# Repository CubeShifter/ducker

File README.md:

# ducker

A nifty pcb that works as a devboard and can do audio, can be battery powered, and also has a lil breakout board for a keyboard switch and a led.

## Description

I have this fidget that whenever you click it, it makes a loud quacking noise, lights up, and is really cool/annoying. I wanted to try to make my own, and this is my second attempt at doing that. When I started making this project, I came into it with these goals
- make it click
- make it make noise
- pretty low power
- can store audio files
- led
- pretty tiny working space
and I managed to do all of those. It uses a CH552(g i think) chip, has 16mb of flash, usb breakout, can contain a lipo and charge it, has a pam 8302 audio amp, can power an led and has a circuit to cut power supply to it. 
## Getting Started
First of all, you need to get it fabbed. I would reccomend ordering from JLCPCB, and you should probably panelize the pcbs because free pcb.  For actual parts I would reference the BOM, they are 805s and stuff so you can probably hand solder it but PCBA is also fine. All production files are in the repo already :3

As of now, there is no official firmware you should flash it with, but there will probably be some soon. This is also a devboard, so you can play around and do whatever you want with it.

## Authors

just me lol, if you want to talk you can email me at kian@shipwrights.dev i guess :3

## Version History

* 0.6
    * pcbs out, 1.0 will probably be firmware + cad

## License

i think it is mit license so do whatever the hell you want with it i dont care, if you do something cool i would love to see it so please reach out at kian@shipwrights.dev

## Acknowledgments

- that one quackey toy thing https://duckeys.com/products/pre-order-quackey-fidget-toy-that-quacks
- the friends we made along the way

## Screenshots
Just putting them here because I don't like how they cover the whole screen.

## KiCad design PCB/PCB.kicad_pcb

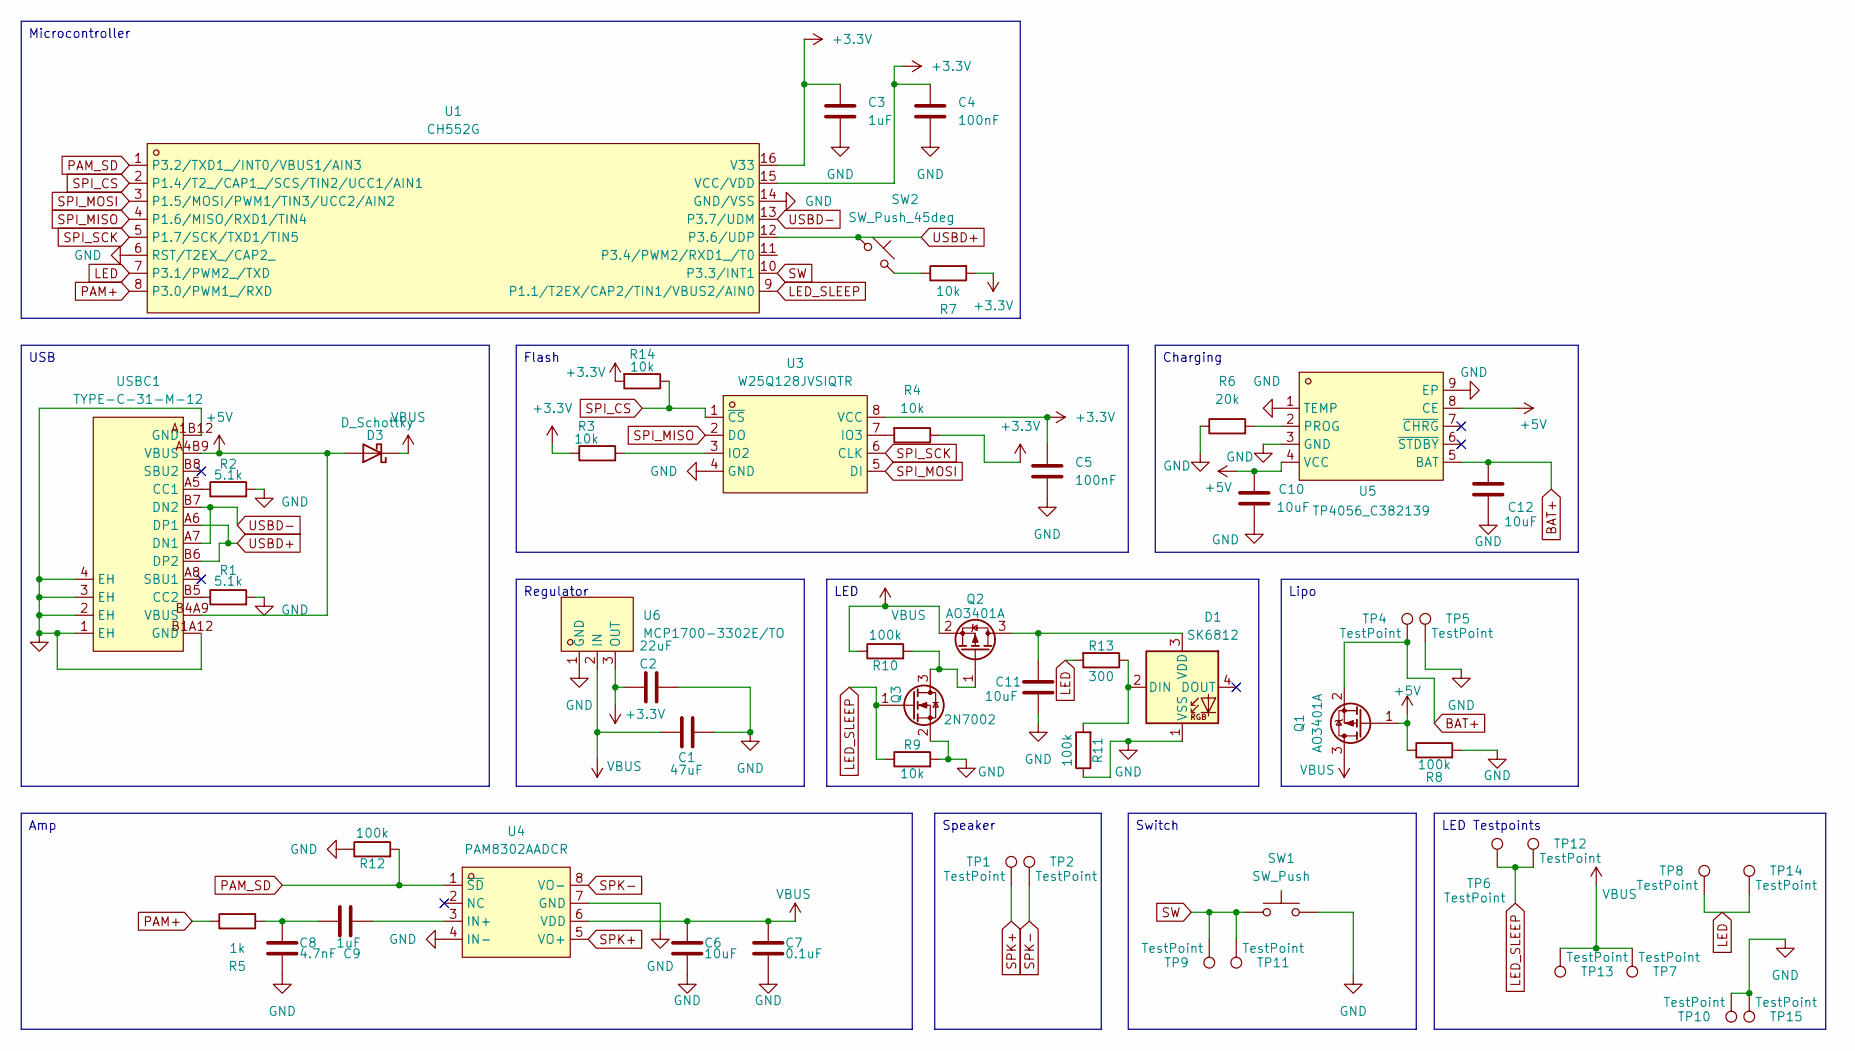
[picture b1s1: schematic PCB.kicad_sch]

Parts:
C1: 47uF; C_0805_2012Metric
C2: 22uF; C_0805_2012Metric
C3, C9: 1uF; C_0805_2012Metric
C4, C5: 100nF; C_0805_2012Metric
C6, C10, C11, C12: 10uF; C_0805_2012Metric
C7: 0.1uF; C_0805_2012Metric
C8: 4.7nF; C_0805_2012Metric
D1: SK6812; LED_SK6812MINI-E_3.2x2.8mm_P1.5mm_ReverseMount
D3: D_Schottky; SOD-123_L2.7-W1.6-LS3.7-RD-1
Q1, Q2: AO3401A; SOT-23
Q3: 2N7002; SOT-23
R1, R2: 5.1k; R_0805_2012Metric
R3, R4, R7, R9, R14: 10k; R_0805_2012Metric
R5: 1k; R_0805_2012Metric
R6: 20k; R_0805_2012Metric
R8, R10, R11, R12: 100k; R_0805_2012Metric
R13: 300; R_0805_2012Metric
SW1: SW_Push; SW_MX_HS_CPG151101S11_1u
SW2: SW_Push_45deg; SW-SMD_L4.0-W3.0-LS5.0
TP1, TP2, TP4, TP5, TP6, TP7, TP8, TP9, TP10, TP11, TP12, TP13, TP14, TP15: TestPoint; TestPoint_Pad_D2.0mm
U1: CH552G; SOP-16_L10.0-W3.9-P1.27-LS6.0-BL; MPN CH552G; LCSC Part C111292
U3: W25Q128JVSIQTR; SOIC-8_L5.3-W5.3-P1.27-LS8.0-BL; MPN W25Q128JVSIQ; LCSC Part C97521
U4: PAM8302AADCR; SOP-8_L4.9-W3.9-P1.27-LS6.0-BL; MPN PAM8302AADCR; LCSC Part C112137
U5: TP4056_C382139; ESOP-8_L4.9-W3.9-P1.27-LS6.0-BL-EP; MPN TP4056; LCSC Part C382139
U6: MCP1700-3302E/TO; TO-92-3_L5.1-W4.1-P1.27-L; MPN MCP1700-3302E/TO; LCSC Part C511277
USBC1: TYPE-C-31-M-12; USB-C_SMD-TYPE-C-31-M-12_1; MPN TYPE-C-31-M-12; LCSC Part C165948

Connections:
+3.3V: C2.1, C3.1, C4.1, C5.1, R3.1, R4.1, R7.2, R14.2, U1.15 (VCC/VDD), U1.16 (V33), U3.8 (VCC), U6.3 (OUT)
+5V: C10.1, D3.2 (A), Q1.1 (G), R8.1, U5.4 (VCC), U5.8 (CE), USBC1.A4B9 (VBUS), USBC1.B4A9 (VBUS)
BAT+: C12.2, Q1.2 (S), TP4.1 (1_1), U5.5 (BAT)
GND: C1.1, C2.2, C3.2, C4.2, C5.2, C6.1, C7.1, C8.1, C10.2, C11.1, C12.1, D1.1 (VSS), Q3.2 (S), R1.2, R2.2, R6.1, R8.2, R9.2, R11.1, R12.1, SW1.2, TP5.1 (1_1), TP10.1 (1_1), TP15.1 (1_1), U1.6 (RST/T2EX_/CAP2_), U1.14 (GND/VSS), U3.4 (GND), U4.4 (IN-), U4.7 (GND), U5.1 (TEMP), U5.3 (GND), U5.9 (EP), U6.1 (GND), USBC1.1 (EH), USBC1.2 (EH), USBC1.3 (EH), USBC1.4 (EH), USBC1.A1B12 (GND), USBC1.B1A12 (GND)
LED: R13.2, TP8.1 (1_1), TP14.1 (1_1), U1.7 (P3.1/PWM2_/TXD)
LED_SLEEP: Q3.1 (G), R9.1, TP6.1 (1_1), TP12.1 (1_1), U1.9 (P1.1/T2EX/CAP2/TIN1/VBUS2/AIN0)
unnamed: C8.2, C9.2, R5.2
unnamed: D1.2 (DIN), R11.2, R13.1
unnamed: C11.2, D1.3 (VDD), Q2.3 (D)
unnamed: Q2.1 (G), Q3.3 (D), R10.2
unnamed: R7.1, SW2.2
unnamed: R3.2, U3.3 (IO2)
unnamed: R4.2, U3.7 (IO3)
unnamed: C9.1, U4.3 (IN+)
unnamed: R6.2, U5.2 (PROG)
unnamed: R2.1, USBC1.A5 (CC1)
unnamed: R1.1, USBC1.B5 (CC2)
PAM+: R5.1, U1.8 (P3.0/PWM1_/RXD)
PAM_SD: R12.2, U1.1 (P3.2/TXD1_/INT0/VBUS1/AIN3), U4.1 (~SD)
SPI_CS: R14.1, U1.2 (P1.4/T2_/CAP1_/SCS/TIN2/UCC1/AIN1), U3.1 (~CS)
SPI_MISO: U1.4 (P1.6/MISO/RXD1/TIN4), U3.2 (DO)
SPI_MOSI: U1.3 (P1.5/MOSI/PWM1/TIN3/UCC2/AIN2), U3.5 (DI)
SPI_SCK: U1.5 (P1.7/SCK/TXD1/TIN5), U3.6 (CLK)
SPK+: TP1.1 (1_1), U4.5 (VO+)
SPK-: TP2.1 (1_1), U4.8 (VO-)
SW: SW1.1, TP9.1 (1_1), TP11.1 (1_1), U1.10 (P3.3/INT1)
USBD+: SW2.1, U1.12 (P3.6/UDP), USBC1.A6 (DP1), USBC1.B6 (DP2)
USBD-: U1.13 (P3.7/UDM), USBC1.A7 (DN1), USBC1.B7 (DN2)
VBUS: C1.2, C6.2, C7.2, D3.1 (K), Q1.3 (D), Q2.2 (S), R10.1, TP7.1 (1_1), TP13.1 (1_1), U4.6 (VDD), U6.2 (IN)

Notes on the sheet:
USB
Lipo
Charging
LED
Amp
Microcontroller
Speaker
Switch
Regulator
LED Testpoints
Flash

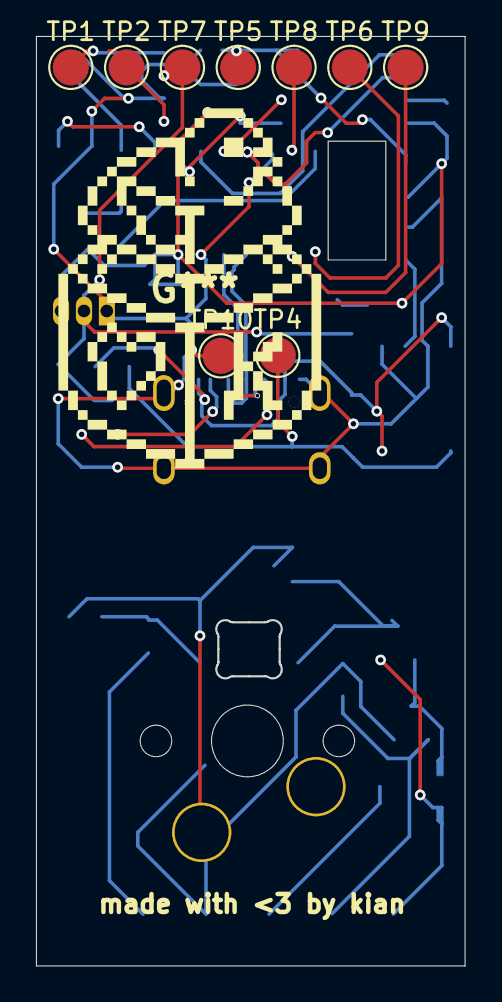
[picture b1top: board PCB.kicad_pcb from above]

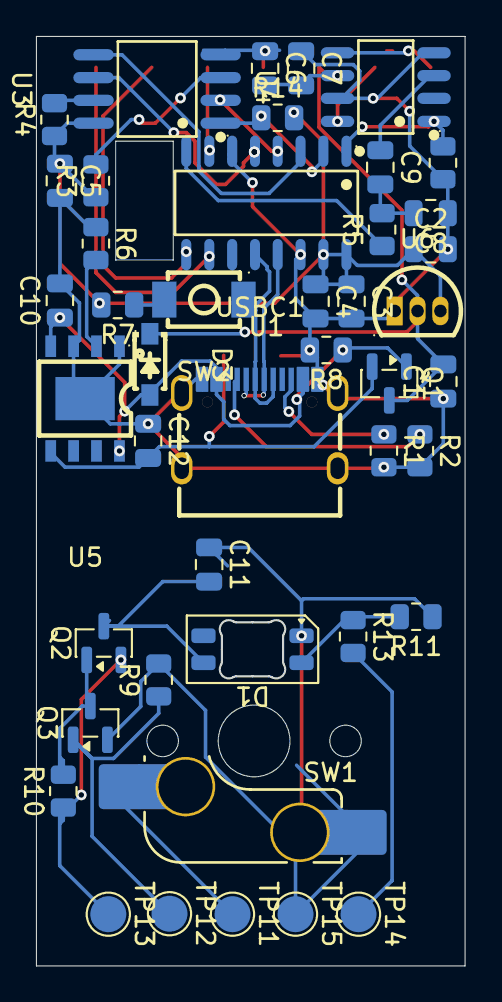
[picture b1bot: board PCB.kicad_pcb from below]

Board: 2 copper layers, 23.8 x 51.6 mm, 53 parts (44 on the bottom side), 29 nets.

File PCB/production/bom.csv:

Designator,Footprint,Quantity,Value,LCSC Part #
C1,0805,1,47uF,
"C10, C11, C12, C6",0805,4,10uF,
C2,0805,1,22uF,
"C3, C9",0805,2,1uF,
"C4, C5",0805,2,100nF,
C7,0805,1,0.1uF,
C8,0805,1,4.7nF,
D1,LED_SK6812MINI-E_3.2x2.8mm_P1.5mm_ReverseMount,1,SK6812,
D3,SOD-123_L2.7-W1.6-LS3.7-RD-1,1,D_Schottky,C150065
"Q1, Q2",SOT-23,2,AO3401A,
Q3,SOT-23,1,2N7002,
"R1, R2",0805,2,5.1k,
"R10, R11, R12, R8",0805,4,100k,
R13,0805,1,300,
"R14, R3, R4, R7, R9",0805,5,10k,
R5,0805,1,1k,
R6,0805,1,20k,
SW1,SW_MX_HS_CPG151101S11_1u,1,SW_Push,
SW2,SW-SMD_L4.0-W3.0-LS5.0,1,SW_Push_45deg,C561517
"TP1, TP10, TP11, TP12, TP13, TP14, TP15, TP2, TP4, TP5, TP6, TP7, TP8, TP9",TestPoint_Pad_D2.0mm,14,TestPoint,
U1,SOP-16_L10.0-W3.9-P1.27-LS6.0-BL,1,CH552G,C111292
U3,SOIC-8_L5.3-W5.3-P1.27-LS8.0-BL,1,W25Q128JVSIQTR,C97521
U4,SOP-8_L4.9-W3.9-P1.27-LS6.0-BL,1,PAM8302AADCR,C112137
U5,ESOP-8_L4.9-W3.9-P1.27-LS6.0-BL-EP,1,TP4056_C382139,C382139
U6,TO-92-3_L5.1-W4.1-P1.27-L,1,MCP1700-3302E/TO,C511277
USBC1,USB-C_SMD-TYPE-C-31-M-12_1,1,TYPE-C-31-M-12,C165948
